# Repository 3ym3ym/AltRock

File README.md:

## Direct Conversion Receiver with signal demodulation in RP2040 ##

This is a low-cost small receiver which plugs into a PC and looks like a soundcard and a CAT interface on the USB port.
The receiver hardware contains: 
- LPF or BPF input filter
- KISS topology I/Q mixer
- Si5351A I/Q LO on a plugin board (Adafruit clone from Aliexpress)
- Discrete transistor 50dB audio preamps, plus additional 15dB gain stages to match the typical signal levels to the ADC input range
- PCM1808 ADC on a plugin board (fake from Aliexpress)
- RP2040-Zero plugin board (same source)

The total BOM can be <$20. 

The input filter is not switched. It can be implemented as a single band BPF, or an LPF to receive a 3x frequency range. For example, a 30MHz LPF allows to receive 10..30MHz. Lower frequencies are received, but there is sensitivity to 3rd harmonic of the LO: when tuned to 7MHz, it will receive both 7 and 21MHz signals.

Schematic and PCB design was done in KiCad. Provided Gerber files can be uploaded to JLCPCB or another PCB manufacturing service.
The PCB is shaped to fit into an Altoids tin. There is a 3D design for an insert to mount the board inside the box. You need to cut holes for the USB connector and your choice of the antenna connector. I punched a 1/4in hole for SMA and soldered it to the inside of the box.

# Firmware #
The heart of the receiver is the firmware that runs on RP2040.
- I2S interface to PCM1808 in master mode, generating necessary clocks
- Demodulates SSB or AM from I/Q
- Audio bandpass filter and AGC
- USB soundcard endpoint, 48kHz/16-bit mono. No drivers required on Windows or Linux.
- Si5351A frequency control
- Software USB serial port endpoint for CAT control, TS-480 command subset
- Another serial port to control parameters which don't have CAT equivalents

A typical use is FT8 monitoring with WSJT-X software. Plug in the receiver, configure WSJT-X to use TS-480 CAT interface and the new soundcard called "Pico", and start monitoring. Band hopping will work within the limits of the installed input filter.

There is also a version of the firmware which doesn't have the demodulator. It presents I/Q raw data to he host PC in stereo 96kHz/16-bit format, for use with SDR software like HDSDR or Quisk.

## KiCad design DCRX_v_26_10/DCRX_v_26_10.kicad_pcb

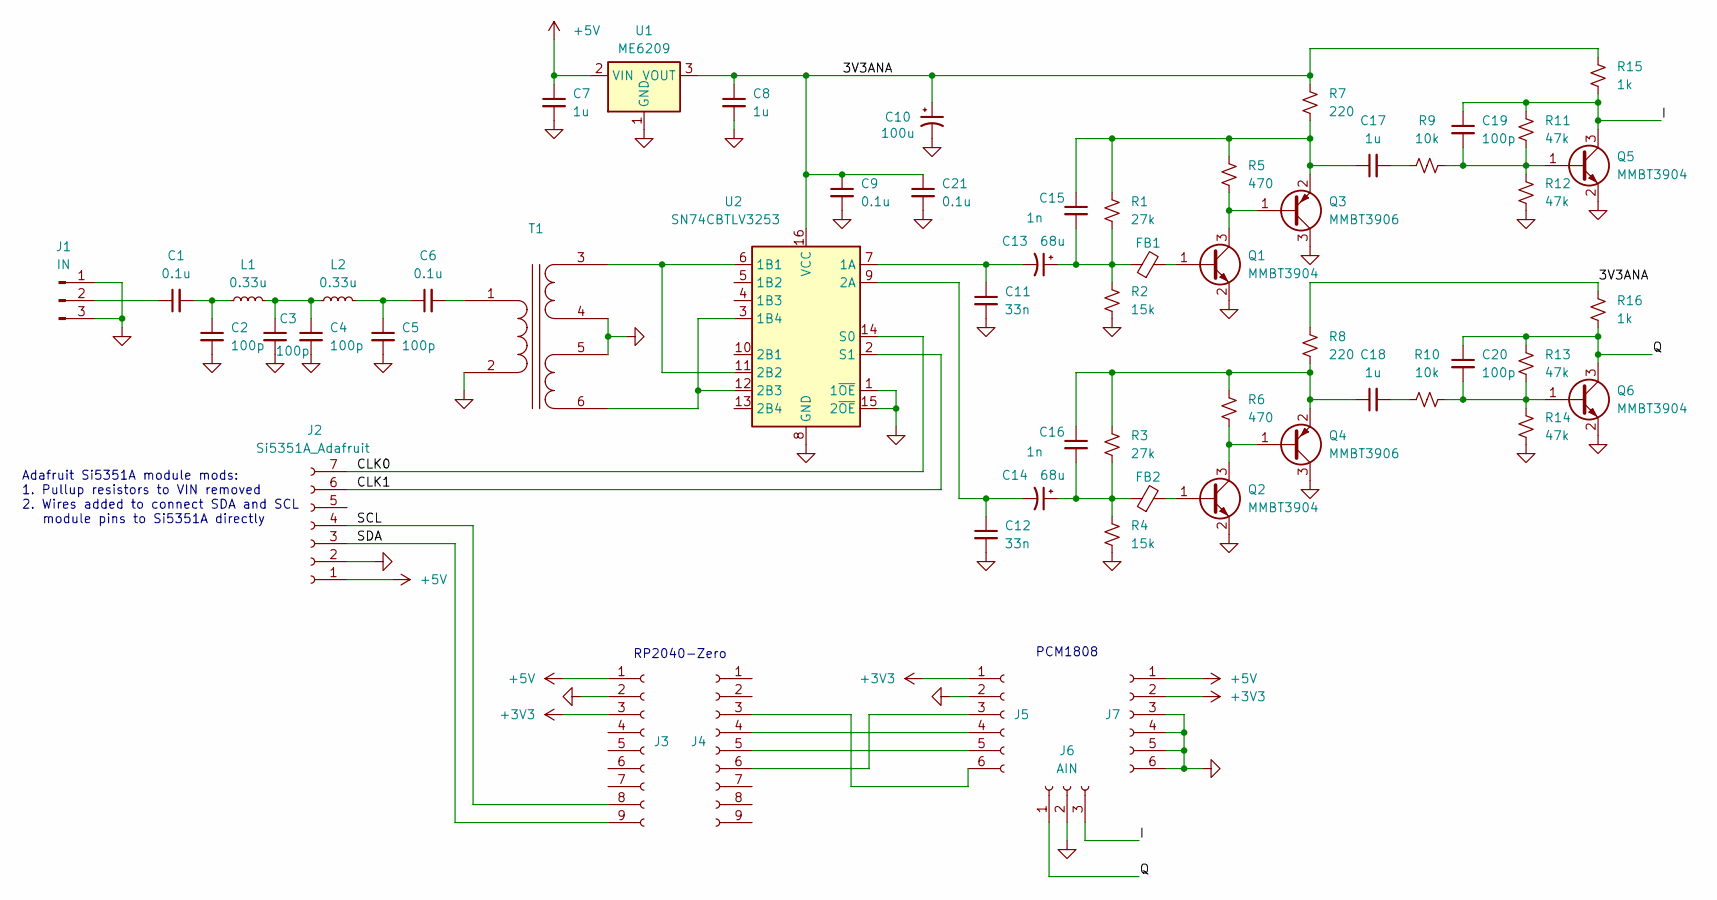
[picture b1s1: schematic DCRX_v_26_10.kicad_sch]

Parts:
C1, C6: 0.1u; C_0805_2012Metric_Pad1.18x1.45mm_HandSolder
C2, C3, C4, C5, C19, C20: 100p; C_0805_2012Metric_Pad1.18x1.45mm_HandSolder
C7, C8, C17, C18: 1u; C_0805_2012Metric_Pad1.18x1.45mm_HandSolder
C9, C21: 0.1u; C_Disc_D3.0mm_W2.0mm_P2.50mm
C10: 100u; CP_Radial_D6.3mm_P2.50mm
C11, C12: 33n; C_Disc_D3.4mm_W2.1mm_P2.50mm
C13, C14: 68u; CP_Radial_D6.3mm_P2.50mm
C15, C16: 1n; C_0805_2012Metric_Pad1.18x1.45mm_HandSolder
FB1, FB2: 100nH; L_0805_2012Metric_Pad1.05x1.20mm_HandSolder
J1: IN; PinHeader_1x03_P2.54mm_Vertical
J2: Si5351A_Adafruit; PinSocket_1x07_P2.54mm_Vertical
J3, J4: Conn_01x09_Socket; PinSocket_1x09_P2.54mm_Vertical
J5, J7: Conn_01x06_Socket; PinSocket_1x06_P2.54mm_Vertical
J6: AIN; PinSocket_1x03_P2.54mm_Vertical
L1, L2: 0.33u; L_Axial_L7.0mm_D3.3mm_P10.16mm_Horizontal_Fastron_MICC
Q1, Q2, Q5, Q6: MMBT3904; SOT-23
Q3, Q4: MMBT3906; SOT-23
R1, R3: 27k; R_0805_2012Metric_Pad1.20x1.40mm_HandSolder
R2, R4: 15k; R_0805_2012Metric_Pad1.20x1.40mm_HandSolder
R5, R6: 470; R_0805_2012Metric_Pad1.20x1.40mm_HandSolder
R7, R8: 220; R_0805_2012Metric_Pad1.20x1.40mm_HandSolder
R9, R10: 10k; R_0805_2012Metric_Pad1.20x1.40mm_HandSolder
R11, R12, R13, R14: 47k; R_0805_2012Metric_Pad1.20x1.40mm_HandSolder
R15, R16: 1k; R_0805_2012Metric_Pad1.20x1.40mm_HandSolder
T1: Transformer_1P_2S; Transformer_Toroid_Tapped_Horizontal_D4.5mm_Amidon-T25
U1: ME6209; SOT-89-3_Handsoldering
U2: SN74CBTLV3253; SO-16_3.9x9.9mm_P1.27mm

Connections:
+3V3: J3.3, J5.1, J7.2
+5V: C7.1, J2.1, J3.1, J7.1, U1.2 (VIN)
/3V3ANA: C8.1, C9.1, C10.1, C21.1, R7.1, R8.1, R15.1, R16.1, U1.3 (VOUT), U2.16 (VCC)
/CLK0: J2.7, U2.14 (S0)
/CLK1: J2.6, U2.2 (S1)
/I: C19.1, J6.3, Q5.3 (C), R11.1, R15.2
/Q: C20.1, J6.1, Q6.3 (C), R13.1, R16.2
/SCL: J2.4, J3.8
/SDA: J2.3, J3.9
GND: C2.2, C3.2, C4.2, C5.2, C7.2, C8.2, C9.2, C10.2, C11.2, C12.2, C21.2, J1.1, J1.3, J2.2, J3.2, J5.2, J6.2, J7.3, J7.4, J7.5, J7.6, Q1.2 (E), Q2.2 (E), Q3.3 (C), Q4.3 (C), Q5.2 (E), Q6.2 (E), R2.2, R4.2, R12.2, R14.2, T1.2 (AB), T1.4 (SB), T1.5 (SC), U1.1 (GND), U2.1 (1~OE), U2.8 (GND), U2.15 (2~OE)
unnamed: C1.2, C2.1, L1.1
unnamed: C3.1, C4.1, L1.2, L2.1
unnamed: C5.1, C6.1, L2.2
unnamed: C13.1, C15.2, FB1.1, R1.2, R2.1
unnamed: C14.1, C16.2, FB2.1, R3.2, R4.1
unnamed: C17.2, R9.1
unnamed: C18.2, R10.1
unnamed: C1.1, J1.2
unnamed: J4.3, J5.6
unnamed: J4.4, J5.4
unnamed: J4.5, J5.5
unnamed: J4.6, J5.3
unnamed: FB1.2, Q1.1 (B)
unnamed: Q1.3 (C), Q3.1 (B), R5.2
unnamed: FB2.2, Q2.1 (B)
unnamed: Q2.3 (C), Q4.1 (B), R6.2
unnamed: C15.1, C17.1, Q3.2 (E), R1.1, R5.1, R7.2
unnamed: C16.1, C18.1, Q4.2 (E), R3.1, R6.1, R8.2
unnamed: C19.2, Q5.1 (B), R9.2, R11.2, R12.1
unnamed: C20.2, Q6.1 (B), R10.2, R13.2, R14.1
unnamed: C6.2, T1.1 (AA)
unnamed: T1.3 (SA), U2.6 (1B1), U2.11 (2B2)
unnamed: T1.6 (SD), U2.3 (1B4), U2.12 (2B3)
unnamed: C11.1, C13.2, U2.7 (1A)
unnamed: C12.1, C14.2, U2.9 (2A)

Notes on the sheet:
RP2040-Zero
PCM1808
Adafruit Si5351A module mods: 1. Pullup resistors to VIN removed 2. Wires added to connect SDA and SCL module pins to Si5351A directly

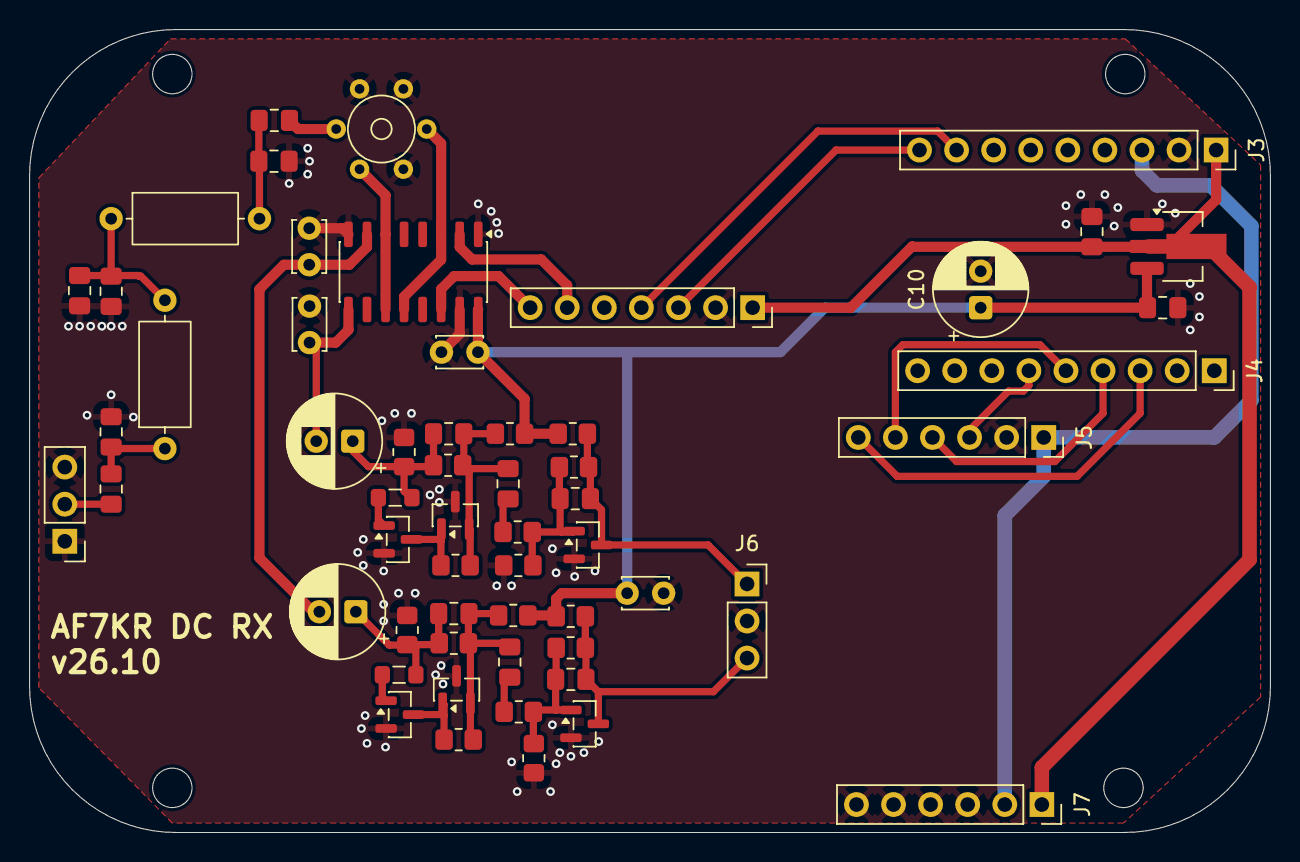
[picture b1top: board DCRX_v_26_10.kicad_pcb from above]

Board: 2 copper layers, 85.0 x 55.0 mm, 57 parts (0 on the bottom side), 35 nets.
